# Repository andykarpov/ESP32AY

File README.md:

# ESP32AY multiformat Turbo Sound player 

## (archived outdated fork, please use the original repo for fresh sources including the PCB)

ESP32 based AY Turbo Sound multiformat player

## Fast flash firmware avaliable on [Alex Spawn OTA web page](https://ota.alexspawn.ru)

## Features
### Supported formats:
- .ayl - [Ay_Emul](https://bulba.untergrund.net/emulator_e.htm) by Sergey Bulba own playlist format
- .pt1 - Pro Tracker v1 file format
- .pt2 - Pro Tracker v2 file format
- .pt3 - Pro Tracker v3 (include Turbo Sound on two AY chips) file format
- .stc - Sound Tracker file format
- .stp - Sound Tracker Pro file format
- .asc - Sound Master file format 
- .psc - Pro Sound Creator file format
- .sqt - SQ Tracker file format
- .ay  - AY file format
- .psg - Programmable Sound Generator file format
- .rsf - Registers Stream Flow file format
- .yrg - [Custom AVR-AY format](https://www.avray.ru/ru/avr-ay-player/)
- UART mode (available in player settings menu as Player source)

### Controls
- Encoder Hold - change mode player/file browser
- Encoder Click - in player mode - play/pause; in file browser mode select track/playlist/directory; select - in config mode
- Encoder Double click - in player mode - open settings
- Encoder Push and turn right - fast forward (for ay format change next subsong)
- Encoder Push and turn left - slow down (for ay format change previous subsong)
- Left button click/hold - volume - (in player mode); cancel - in config mode
- Right button click/hold - volume + (in player mode)
- Left button double click - change AY clock (in player mode)
- Right button double click - change play mode: all/shuffle/once (in player mode)

### Playing modes:
- Playing all tracks (in folder/playlist)
- Playing random track (in folder/playlist)
- Playing once track (loop)

### Supports fully realtime file browser

### Supports realtime AY layers change:
- ABC
- ACB
- BAC
- BCA
- CAB
- CBA

### Supports realtime AY clock change:
- ZX SPECTRUM - 1773400 Hz
- PENTAGON - 1750000 Hz
- MSX - 1789772 Hz
- CPC - 1000000 Hz
- ATARI ST - 2000000 Hz

### Built-in battery

### Built-in charger and indication on LED and TFT

### Built-in headphones stereo amplifier controlled by I2C bus

## Demo video with digital sound record:

### UPD 22.10.2024
- Add new feature: "UART mode" with AVR-AY player through UART.

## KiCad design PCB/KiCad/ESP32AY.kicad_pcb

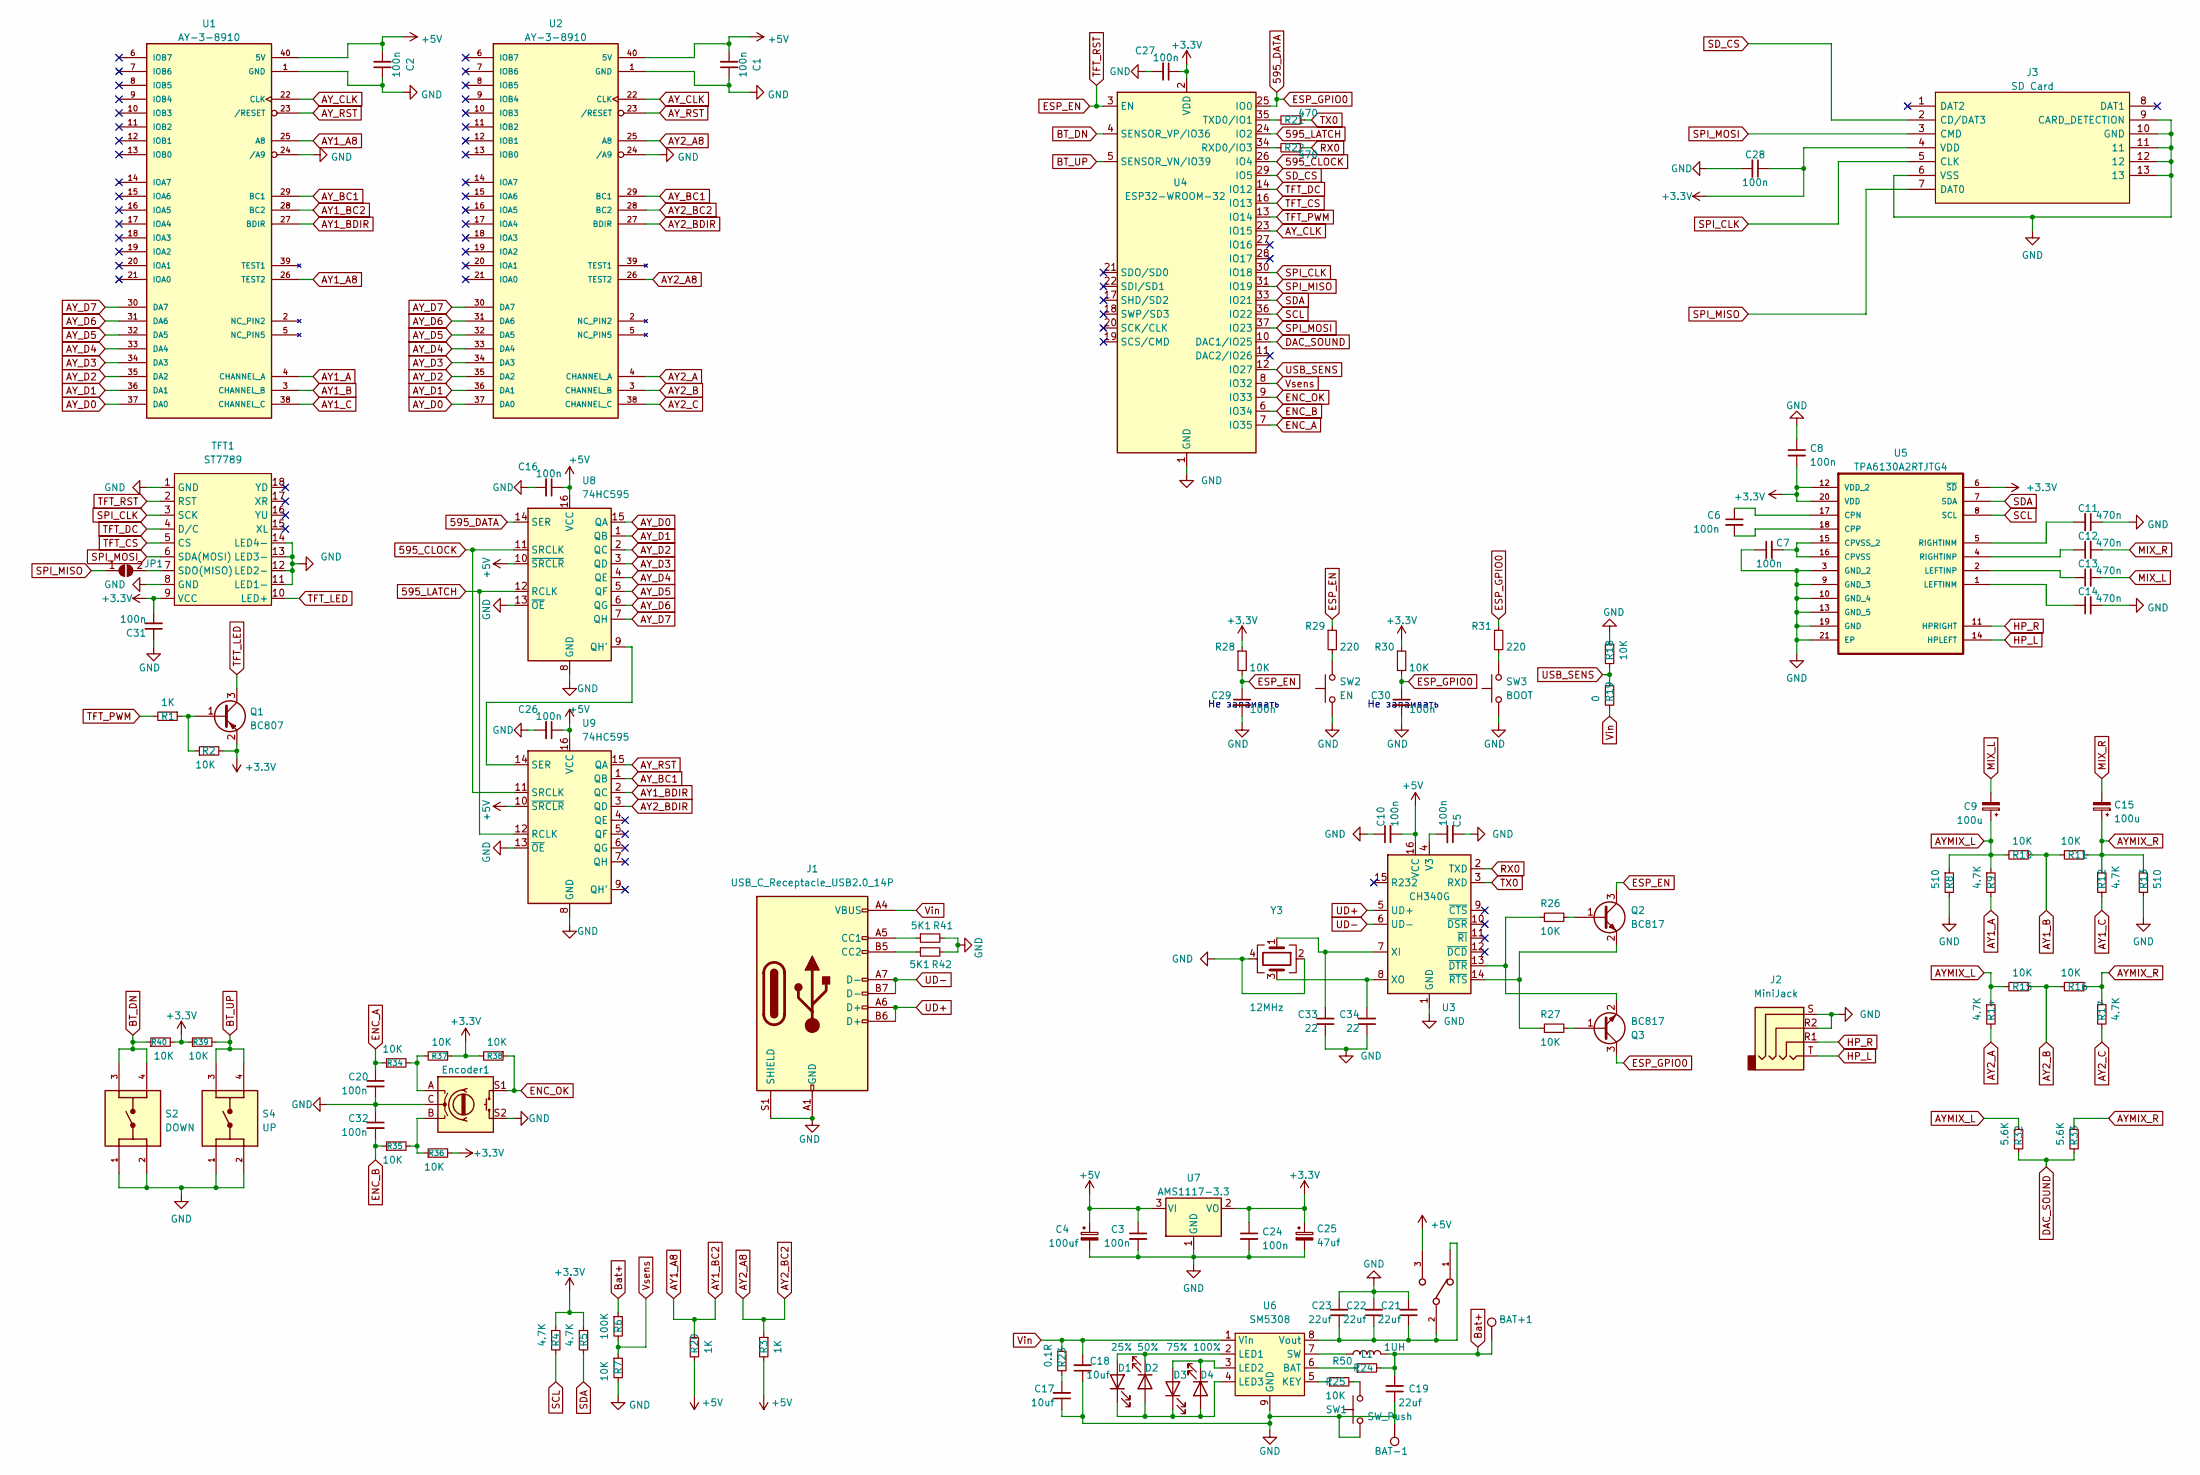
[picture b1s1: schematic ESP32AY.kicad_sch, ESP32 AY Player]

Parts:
BAT+1: BAT+; TestPoint_Pad_D3.0mm
BAT-1: BAT-; TestPoint_Pad_D3.0mm
C1, C2, C3, C5, C6, C7, C8, C10, C16, C20, C24, C26, C27, C28, C29, C30, C31, C32: 100n; C_0805_2012Metric_Pad1.18x1.45mm_HandSolder
C4: 100uf; CP_EIA-7343-31_Kemet-D-uni
C9, C15: 100u; CP_EIA-7343-31_Kemet-D_Pad2.25x2.55mm_HandSolder
C11, C12, C13, C14: 470n; C_0805_2012Metric_Pad1.18x1.45mm_HandSolder
C17, C18: 10uf; C_0805_2012Metric_Pad1.18x1.45mm_HandSolder
C19, C21, C22: 22uf; C_0805_2012Metric_Pad1.18x1.45mm_HandSolder
C23: 22uf; C_0805_2012Metric
C25: 47uf; CP_EIA-7343-31_Kemet-D-uni
C33, C34: 22; C_0805_2012Metric_Pad1.18x1.45mm_HandSolder
D1: 25%; LED_0805_2012Metric
D2: 50%; LED_0805_2012Metric
D3: 75%; LED_0805_2012Metric
D4: 100%; LED_0805_2012Metric
Encoder1: RotaryEncoder_Switch; RotaryEncoder_Alps_EC11E-Switch_Vertical_H20mm
J1: USB_C_Receptacle_USB2.0_14P; USB_C_Receptacle_G-Switch_GT-USB-7010ASV
J2: MiniJack; AUDIO_JACK_3.5MM_SMD_TRRS_rounded_mixed
J3: SD Card; TFP09212B; Manufacturer_Part_Number TFP09-2-12B
JP1: jumper; SolderJumper-2_P1.3mm_Bridged_RoundedPad1.0x1.5mm
L1: 1UH; L_7.3x7.3_H3.5
Q1: BC807; SOT-23
Q2, Q3: BC817; SOT-23
R1, R3, R20: 1K; R_0805_2012Metric_Pad1.20x1.40mm_HandSolder
R2, R7, R10, R11, R15, R16, R18, R26, R27, R28, R30, R34, R35, R36, R37, R38, R39, R40: 10K; R_0805_2012Metric_Pad1.20x1.40mm_HandSolder
R4, R5, R9, R12, R14, R17: 4.7K; R_0805_2012Metric_Pad1.20x1.40mm_HandSolder
R6: 100K; R_0805_2012Metric_Pad1.20x1.40mm_HandSolder
R8, R13: 510; R_0805_2012Metric_Pad1.20x1.40mm_HandSolder
R19: 0; R_0805_2012Metric_Pad1.20x1.40mm_HandSolder
R21, R22: 470; R_0805_2012Metric_Pad1.20x1.40mm_HandSolder
R23: 0.1R; R_0805_2012Metric
R24: R50; R_0805_2012Metric
R25: 10K; R_0805_2012Metric
R29, R31: 220; R_0805_2012Metric_Pad1.20x1.40mm_HandSolder
R32, R33: 5.6K; R_0805_2012Metric_Pad1.20x1.40mm_HandSolder
R41, R42: 5K1; R_0805_2012Metric_Pad1.20x1.40mm_HandSolder
S2: DOWN; SW_Push_1P1T_NO_6x6mm_H9.5mm
S4: UP; SW_Push_1P1T_NO_6x6mm_H9.5mm
S6: EG1213; SW_EG1213
SW1: SW_Push; SolderJumper-2_P1.3mm_Open_RoundedPad1.0x1.5mm
SW2: EN; SW_SPST_PTS810_handsoldering
SW3: BOOT; SW_SPST_PTS810_handsoldering
TFT1: ST7789
U1, U2: AY-3-8910; DIP-40_W15.24mm_Socket
U3: CH340G; SOIC-16_3.9x9.9mm_P1.27mm
U4: ESP32-WROOM-32
U5: TPA6130A2RTJTG4; QFN50P400X400X80-21N; MPN TPA6130A2RTJTG4
U6: SM5308; HSOP-8-1EP_3.9x4.9mm_P1.27mm_EP2.41x3.1mm
U7: AMS1117-3.3; SOT-223-3_TabPin2
U8, U9: 74HC595; SO-16_5.3x10.2mm_P1.27mm
Y3: 12MHz; Crystal_SMD_3225-4Pin_3.2x2.5mm_HandSoldering; PARTREV 10/24/2022

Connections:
595_CLOCK: U4.26 (IO4), U8.11 (SRCLK), U9.11 (SRCLK)
595_DATA: C30.1, Q3.3 (C), R30.2, R31.1, U4.25 (IO0), U8.14 (SER)
595_LATCH: U4.24 (IO2), U8.12 (RCLK), U9.12 (RCLK)
+3.3V: C8.2, C24.1, C25.1, C27.1, C28.1, C31.2, J3.4 (VDD), Q1.2 (E), R2.2, R4.1, R5.1, R28.1, R30.1, R36.2, R37.1, R38.2, R39.1, R40.2, TFT1.9 (VCC), U4.2 (VDD), U5.6 (~SD), U5.12 (VDD_2), U5.20 (VDD), U7.2 (VO)
+5V: C1.2, C2.2, C3.1, C4.1, C10.2, C16.1, C26.1, R3.2, R20.2, S6.3, U1.40 (5V), U2.40 (5V), U3.16 (VCC), U7.3 (VI), U8.10 (~SRCLR), U8.16 (VCC), U9.10 (~SRCLR), U9.16 (VCC)
AY1_A: R9.2, U1.4 (CHANNEL_A)
AY1_A8: R20.1, U1.25 (A8), U1.26 (TEST2), U1.28 (BC2)
AY1_B: R10.1, R11.2, U1.3 (CHANNEL_B)
AY1_BDIR: U1.27 (BDIR), U9.2 (QC)
AY1_C: R12.2, U1.38 (CHANNEL_C)
AY2_A: R14.2, U2.4 (CHANNEL_A)
AY2_A8: R3.1, U2.25 (A8), U2.26 (TEST2), U2.28 (BC2)
AY2_B: R15.1, R16.2, U2.3 (CHANNEL_B)
AY2_BDIR: U2.27 (BDIR), U9.3 (QD)
AY2_C: R17.2, U2.38 (CHANNEL_C)
AYMIX_L: C9.1, R8.1, R9.1, R10.2, R14.1, R15.2, R32.1
AYMIX_R: C15.1, R11.1, R12.1, R13.1, R16.1, R17.1, R33.1
AY_BC1: U1.29 (BC1), U2.29 (BC1), U9.1 (QB)
AY_CLK: U1.22 (CLK), U2.22 (CLK), U4.23 (IO15)
AY_D0: U1.37 (DA0), U2.37 (DA0), U8.15 (QA)
AY_D1: U1.36 (DA1), U2.36 (DA1), U8.1 (QB)
AY_D2: U1.35 (DA2), U2.35 (DA2), U8.2 (QC)
AY_D3: U1.34 (DA3), U2.34 (DA3), U8.3 (QD)
AY_D4: U1.33 (DA4), U2.33 (DA4), U8.4 (QE)
AY_D5: U1.32 (DA5), U2.32 (DA5), U8.5 (QF)
AY_D6: U1.31 (DA6), U2.31 (DA6), U8.6 (QG)
AY_D7: U1.30 (DA7), U2.30 (DA7), U8.7 (QH)
AY_RST: U1.23 (/RESET), U2.23 (/RESET), U9.15 (QA)
BT_DN: R40.1, S2.3, S2.4, U4.4 (SENSOR_VP/IO36)
BT_UP: R39.2, S4.3, S4.4, U4.5 (SENSOR_VN/IO39)
Bat+: BAT+1.1, C19.2, L1.2, R6.1, R24.2
DAC_SOUND: R32.2, R33.2, U4.10 (DAC1/IO25)
ENC_A: C20.1, R34.1, U4.7 (IO35)
ENC_B: C32.2, R35.1, U4.6 (IO34)
ENC_OK: Encoder1.S1, R38.1, U4.9 (IO33)
ESP_EN: C29.1, Q2.3 (C), R28.2, R29.1, TFT1.2 (RST), U4.3 (EN)
GND: BAT-1.1, C1.1, C2.1, C3.2, C4.2, C5.1, C7.1, C8.1, C10.1, C11.1, C14.2, C16.2, C17.1, C18.1, C19.1, C20.2, C21.2, C22.2, C23.2, C24.2, C25.2, C26.2, C27.2, C28.2, C29.2, C30.2, C31.1, C32.1, C33.1, C34.1, Encoder1.C, Encoder1.S2, J1.A1 (GND), J1.A12 (GND), J1.B1 (GND), J1.B12 (GND), J1.S1 (SHIELD), J2.R2, J2.S, J3.6 (VSS), J3.9 (CARD_DETECTION), J3.10 (GND), J3.11, J3.12, J3.13, R7.2, R8.2, R13.2, R18.1, R41.2, R42.2, S2.1, S2.2, S4.1, S4.2, SW1.1, SW2.1 (A), SW3.1 (A), TFT1.1 (GND), TFT1.8 (GND), TFT1.11 (LED1-), TFT1.12 (LED2-), TFT1.13 (LED3-), TFT1.14 (LED4-), U1.1 (GND), U1.24 (/A9), U2.1 (GND), U2.24 (/A9), U3.1 (GND), U4.1 (GND), U4.15 (GND), U4.38 (GND), U4.39 (GND), U5.3 (GND_2), U5.9 (GND_3), U5.10 (GND_4), U5.13 (GND_5), U5.19 (GND), U5.21 (EP), U6.9 (GND), U7.1 (GND), U8.8 (GND), U8.13 (~OE), U9.8 (GND), U9.13 (~OE), Y3.2, Y3.4
HP_L: J2.T, U5.14 (HPLEFT)
HP_R: J2.R1, U5.11 (HPRIGHT)
MIX_L: C9.2, C13.2
MIX_R: C12.2, C15.2
unnamed: C17.2, R23.2
unnamed: D1.2 (A), D2.1 (K), U6.2 (LED1)
unnamed: D1.1 (K), D2.2 (A), D3.1 (K), D4.2 (A), U6.4 (LED3)
unnamed: D3.2 (A), D4.1 (K), U6.3 (LED2)
unnamed: Encoder1.A, R34.2, R37.2
unnamed: Encoder1.B, R35.2, R36.1
unnamed: J1.A5 (CC1), R41.1
unnamed: J1.B5 (CC2), R42.1
unnamed: JP1.2 (B), TFT1.7 (SDO(MISO))
unnamed: Q1.1 (B), R1.1, R2.1
unnamed: Q2.1 (B), R26.2
unnamed: Q2.2 (E), R27.1, U3.14 (~RTS)
unnamed: Q3.1 (B), R27.2
unnamed: Q3.2 (E), R26.1, U3.13 (~DTR)
unnamed: R25.2, SW1.2
unnamed: R29.2, SW2.2 (B)
unnamed: R31.2, SW3.2 (B)
unnamed: C5.2, U3.4 (V3)
unnamed: C33.2, U3.7 (XI), Y3.1
unnamed: C34.2, U3.8 (XO), Y3.3
unnamed: R22.2, U4.34 (RXD0/IO3)
unnamed: R21.2, U4.35 (TXD0/IO1)
unnamed: C6.1, U5.17 (CPN)
unnamed: C6.2, U5.18 (CPP)
unnamed: C7.2, U5.15 (CPVSS_2), U5.16 (CPVSS)
unnamed: C14.1, U5.1 (LEFTINM)
unnamed: C13.1, U5.2 (LEFTINP)
unnamed: C11.2, U5.5 (RIGHTINM)
unnamed: C12.1, U5.4 (RIGHTINP)
unnamed: R24.1, U6.6 (BAT)
unnamed: R25.1, U6.5 (KEY)
unnamed: L1.1, U6.7 (SW)
unnamed: C21.1, C22.1, C23.1, S6.1, S6.2, U6.8 (Vout)
unnamed: U8.9 (QH'), U9.14 (SER)
RX0: R22.1, U3.2 (TXD)
SCL: R4.2, U4.36 (IO22), U5.8 (SCL)
SDA: R5.2, U4.33 (IO21), U5.7 (SDA)
SD_CS: J3.2 (CD/DAT3), U4.29 (IO5)
SPI_CLK: J3.5 (CLK), TFT1.3 (SCK), U4.30 (IO18)
SPI_MISO: J3.7 (DAT0), JP1.1 (A), U4.31 (IO19)
SPI_MOSI: J3.3 (CMD), TFT1.6 (SDA(MOSI)), U4.37 (IO23)
TFT_CS: TFT1.5 (CS), U4.16 (IO13)
TFT_DC: TFT1.4 (D/C), U4.14 (IO12)
TFT_LED: Q1.3 (C), TFT1.10 (LED+)
TFT_PWM: R1.2, U4.13 (IO14)
TX0: R21.1, U3.3 (RXD)
UD+: J1.A6 (D+), J1.B6 (D+), U3.5 (UD+)
UD-: J1.A7 (D-), J1.B7 (D-), U3.6 (UD-)
USB_SENS: R18.2, R19.1, U4.12 (IO27)
Vin: C18.2, J1.A4 (VBUS), J1.A9 (VBUS), J1.B4 (VBUS), J1.B9 (VBUS), R19.2, R23.1, U6.1 (Vin)
Vsens: R6.2, R7.1, U4.8 (IO32)

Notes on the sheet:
Не запаивать

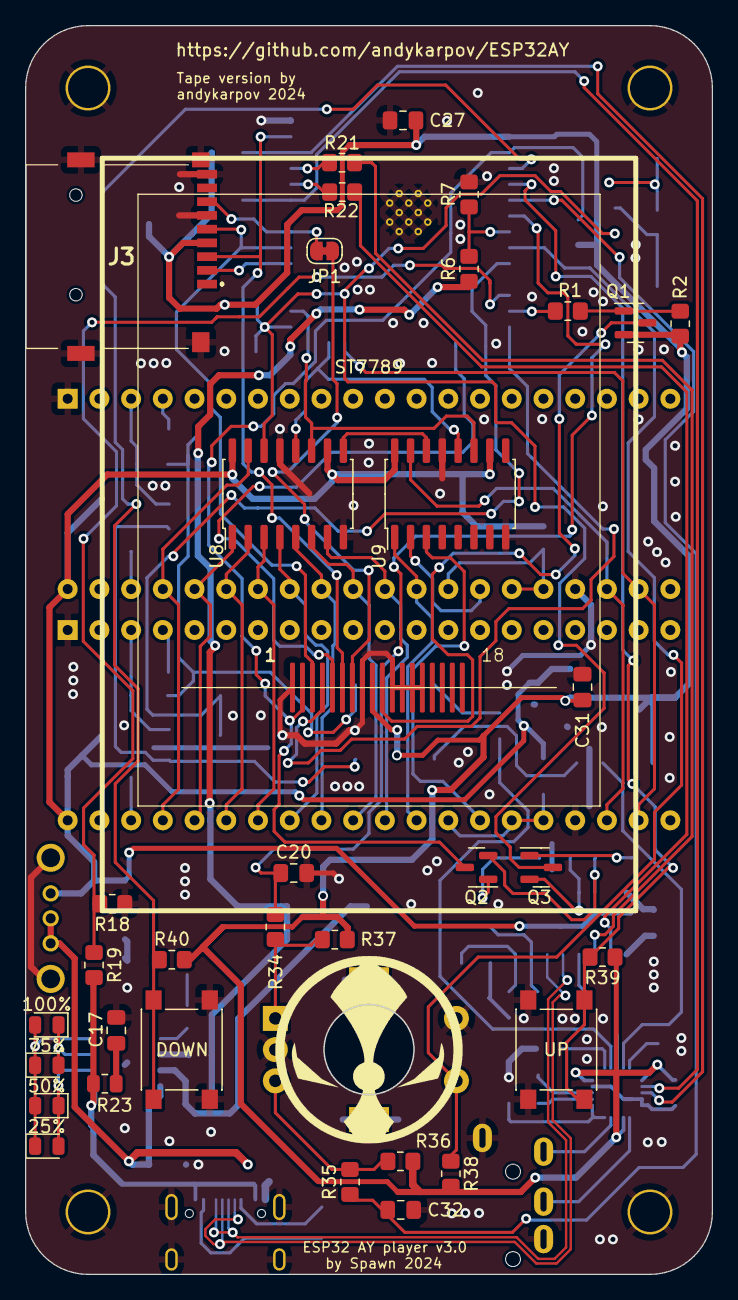
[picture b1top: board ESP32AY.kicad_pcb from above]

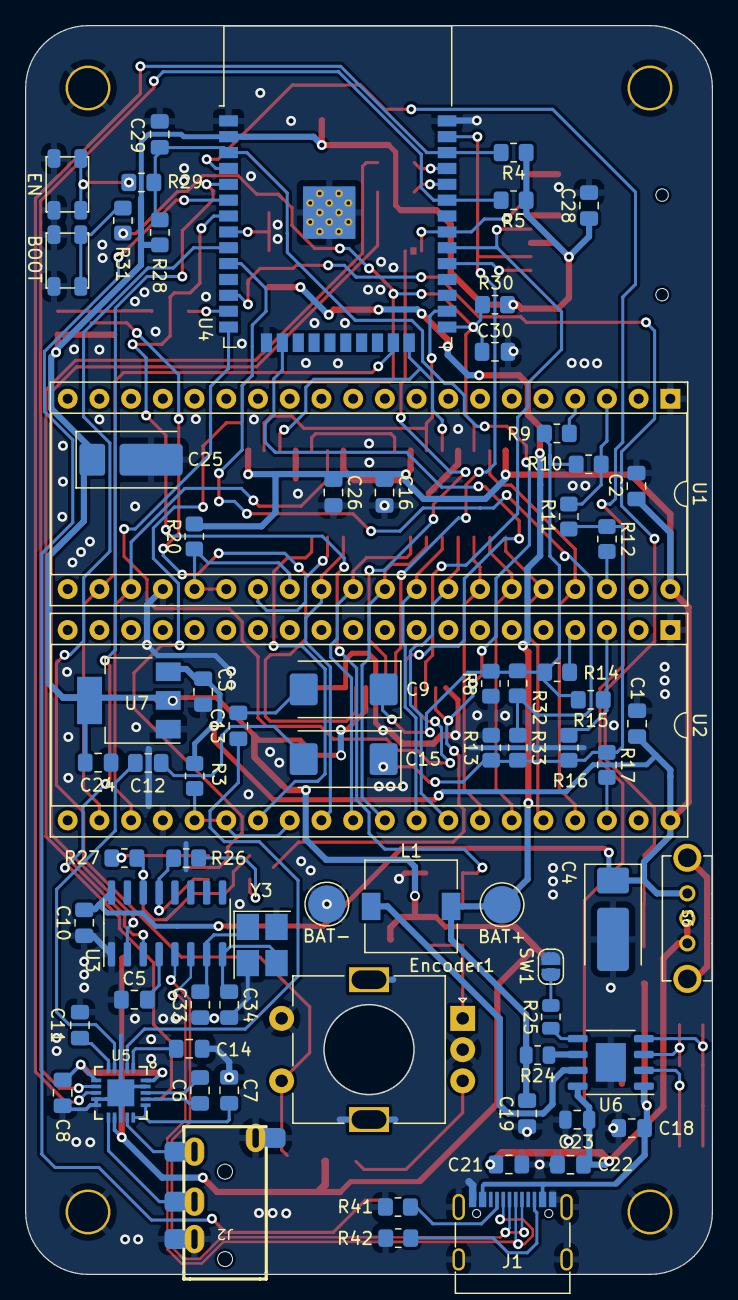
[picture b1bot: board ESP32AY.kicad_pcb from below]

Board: 2 copper layers, 55.0 x 100.0 mm, 108 parts (72 on the bottom side), 92 nets.

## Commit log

2024-10-02 Replaced miniUSB with typeC, changed small buttons, changed 12MHz crystal footprint
2024-10-03 Replaced 1206 to 0805 hand soldering footprints
2024-10-03 OpenSCAD project and top case with bigger hole for type-c
2024-10-03 Changed tantalum cap footprints
2024-10-04 Small silskreen fixes, moved tiny buttons on the one side
2024-10-25 upstream sync (#3)
    * udate encButton library
    * upate version build
    * add: new feature - Playing over UART
    * update: firmware with v3.2
    * update readme
    * fix: settings menu bug
